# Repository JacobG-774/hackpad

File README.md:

# Tuxpad!
*A 6-key macropad with an OLED display, neopixel light bar, and circuitpython firmware, designed to simplify repetitive tasks.*

[PCB demo on KiCanvas](https://kicanvas.org/?repo=https%3A%2F%2Fgithub.com%2FJacobG-774%2Fhackpad%2Fblob%2Fmain%2FPCB%2Fhackpad.kicad_pcb)

**Features**

* Customizable macros to simplify productivity, gaming, or other workflows/applications
* RGB Neopixel bar for awesome customizable lighting
* OLED display for time, system information, or motivational messages

**Materials Used**

* Seeed XIAO RP2040 microcontroller - 1
* MX-style mechanical switches - 6
* 0.91” 128×32 OLED display - 1
* Blank DSA keycaps - 6
* SK6812 MINI-E RGB LEDs - 16
* M3×16mm screws - 4
In addition to the PCB and 3d printed case of course.

**How it Works**

I decided on direct wiring for the switches as matrix wiring would add complication and more possible failure points to the design while only saving one pin (which I wouldn't need anyways). The Neopixel LEDs can be individually controlled through the firmware and allow for full and relatively simple customizability. 
My choice of CircuitPython without KMK for the firmware might seem counterintuitive, but this enables me to more easily base lighting patterns or displays on the LCD off key presses (for example, the neopixels change color every key press, or the LCD displays my total key press count for the day to keep me motivated). I also couldn't find any documentation for direct wiring, OLED, or LED support in KMK, so it wasn't a very viable option.

**Credits/Acknowledgements**

I'm happy to say I mostly designed my case and PCB with just the help of the Hackpad tutorial, Google, and my few brain cells. The rendering was made with the help of [ohagel](https://www.thingiverse.com/thing:738769) and [gcb](https://www.thingiverse.com/thing:421524)'s files on Thingiverse, and I used a small amount of AI and reverse engineering from [LyricSantana](https://github.com/LyricSantana/lyrics_macropad/tree/main)'s code for the firmware.

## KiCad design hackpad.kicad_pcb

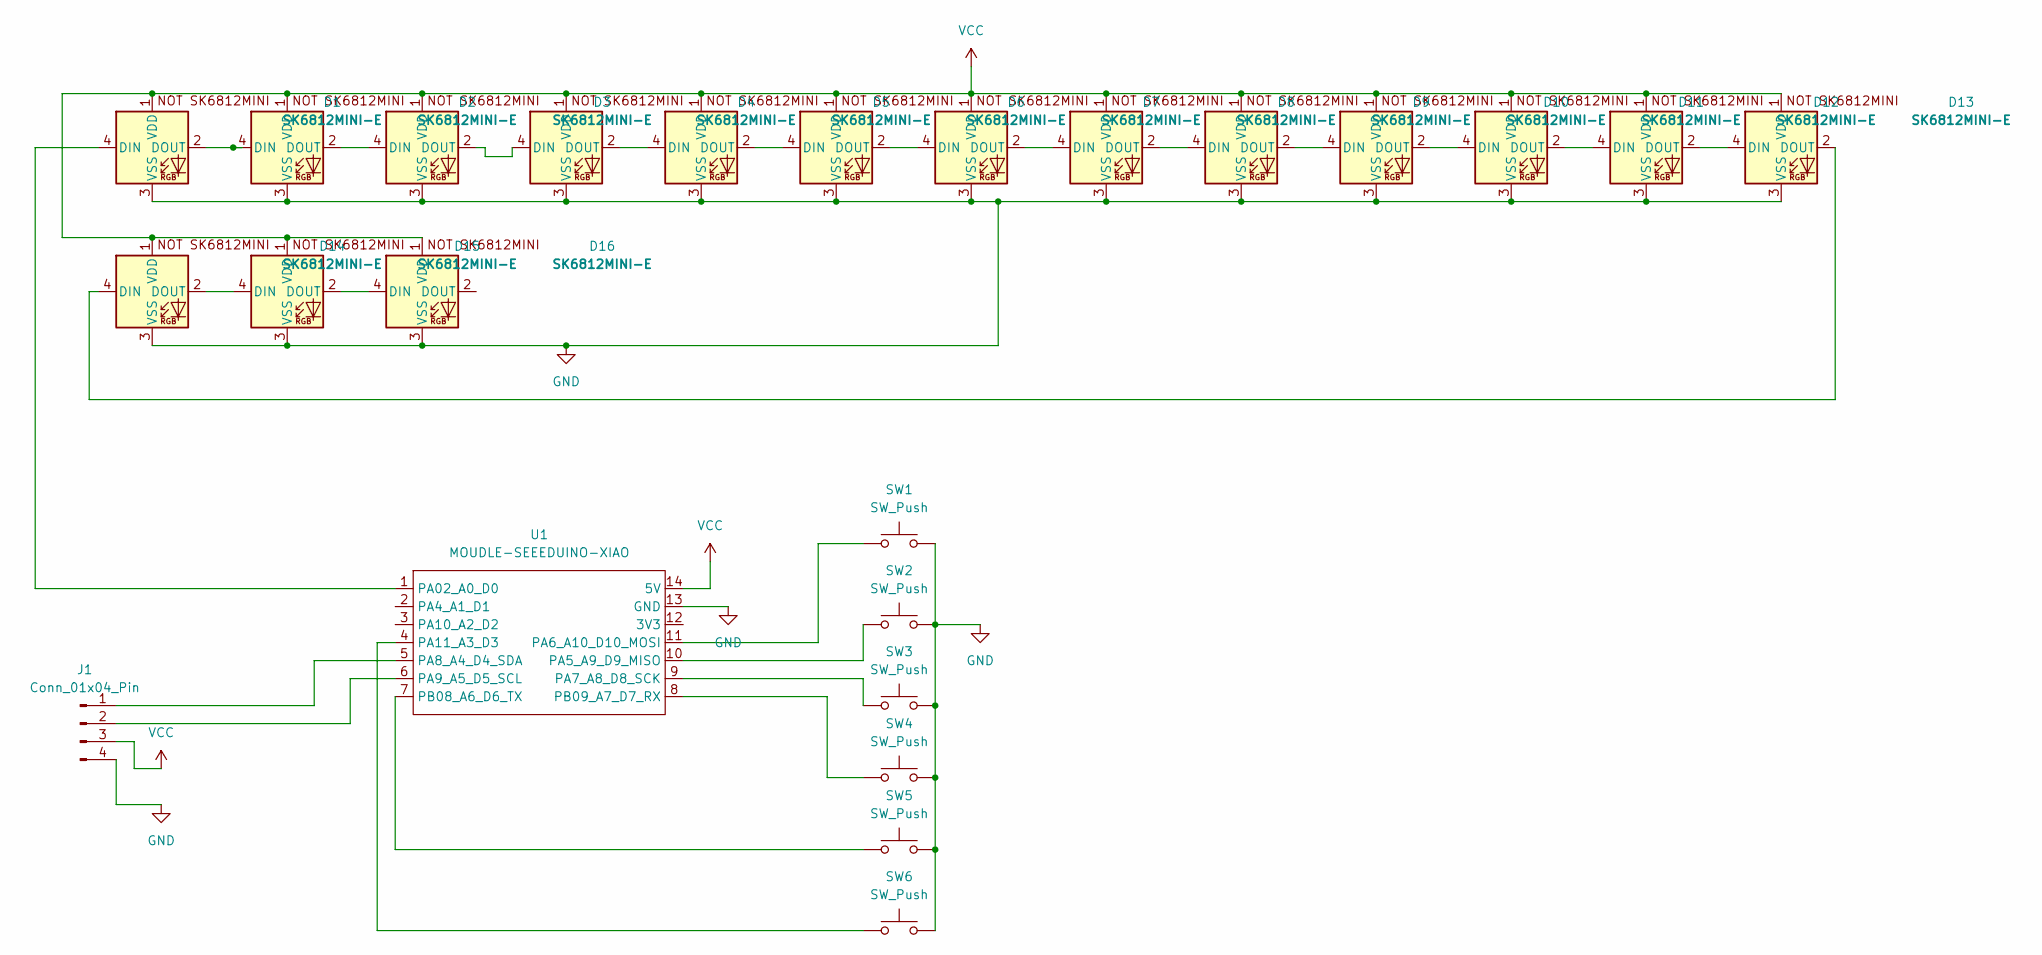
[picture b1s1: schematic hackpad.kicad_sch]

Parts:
D1, D2, D3, D4, D5, D6, D7, D8, D9, D10, D11, D12, D13, D14, D15, D16: SK6812MINI-E; SK6812MINI-E_fixed
J1: Conn_01x04_Pin; PinHeader_1x04_P2.54mm_Vertical
SW1, SW2, SW3, SW4, SW5, SW6: SW_Push; SW_Cherry_MX_1.00u_PCB
U1: MOUDLE-SEEEDUINO-XIAO; XIAO-Generic-Hybrid-14P-2.54-21X17.8MM

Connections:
GND: D1.3 (VSS), D2.3 (VSS), D3.3 (VSS), D4.3 (VSS), D5.3 (VSS), D6.3 (VSS), D7.3 (VSS), D8.3 (VSS), D9.3 (VSS), D10.3 (VSS), D11.3 (VSS), D12.3 (VSS), D13.3 (VSS), D14.3 (VSS), D15.3 (VSS), D16.3 (VSS), J1.4, SW1.2, SW2.2, SW3.2, SW4.2, SW5.2, SW6.2, U1.13 (GND)
unnamed: D1.4 (DIN), U1.1 (PA02_A0_D0)
unnamed: D1.2 (DOUT), D2.4 (DIN)
unnamed: D2.2 (DOUT), D3.4 (DIN)
unnamed: D3.2 (DOUT), D4.4 (DIN)
unnamed: D4.2 (DOUT), D5.4 (DIN)
unnamed: D5.2 (DOUT), D6.4 (DIN)
unnamed: D6.2 (DOUT), D7.4 (DIN)
unnamed: D7.2 (DOUT), D8.4 (DIN)
unnamed: D8.2 (DOUT), D9.4 (DIN)
unnamed: D9.2 (DOUT), D10.4 (DIN)
unnamed: D10.2 (DOUT), D11.4 (DIN)
unnamed: D11.2 (DOUT), D12.4 (DIN)
unnamed: D12.2 (DOUT), D13.4 (DIN)
unnamed: D13.2 (DOUT), D14.4 (DIN)
unnamed: D14.2 (DOUT), D15.4 (DIN)
unnamed: D15.2 (DOUT), D16.4 (DIN)
unnamed: J1.1, U1.5 (PA8_A4_D4_SDA)
unnamed: J1.2, U1.6 (PA9_A5_D5_SCL)
unnamed: SW2.1, U1.10 (PA5_A9_D9_MISO)
unnamed: SW1.1, U1.11 (PA6_A10_D10_MOSI)
unnamed: SW3.1, U1.9 (PA7_A8_D8_SCK)
unnamed: SW6.1, U1.4 (PA11_A3_D3)
unnamed: SW5.1, U1.7 (PB08_A6_D6_TX)
unnamed: SW4.1, U1.8 (PB09_A7_D7_RX)
VCC: D1.1 (VDD), D2.1 (VDD), D3.1 (VDD), D4.1 (VDD), D5.1 (VDD), D6.1 (VDD), D7.1 (VDD), D8.1 (VDD), D9.1 (VDD), D10.1 (VDD), D11.1 (VDD), D12.1 (VDD), D13.1 (VDD), D14.1 (VDD), D15.1 (VDD), D16.1 (VDD), J1.3, U1.14 (5V)

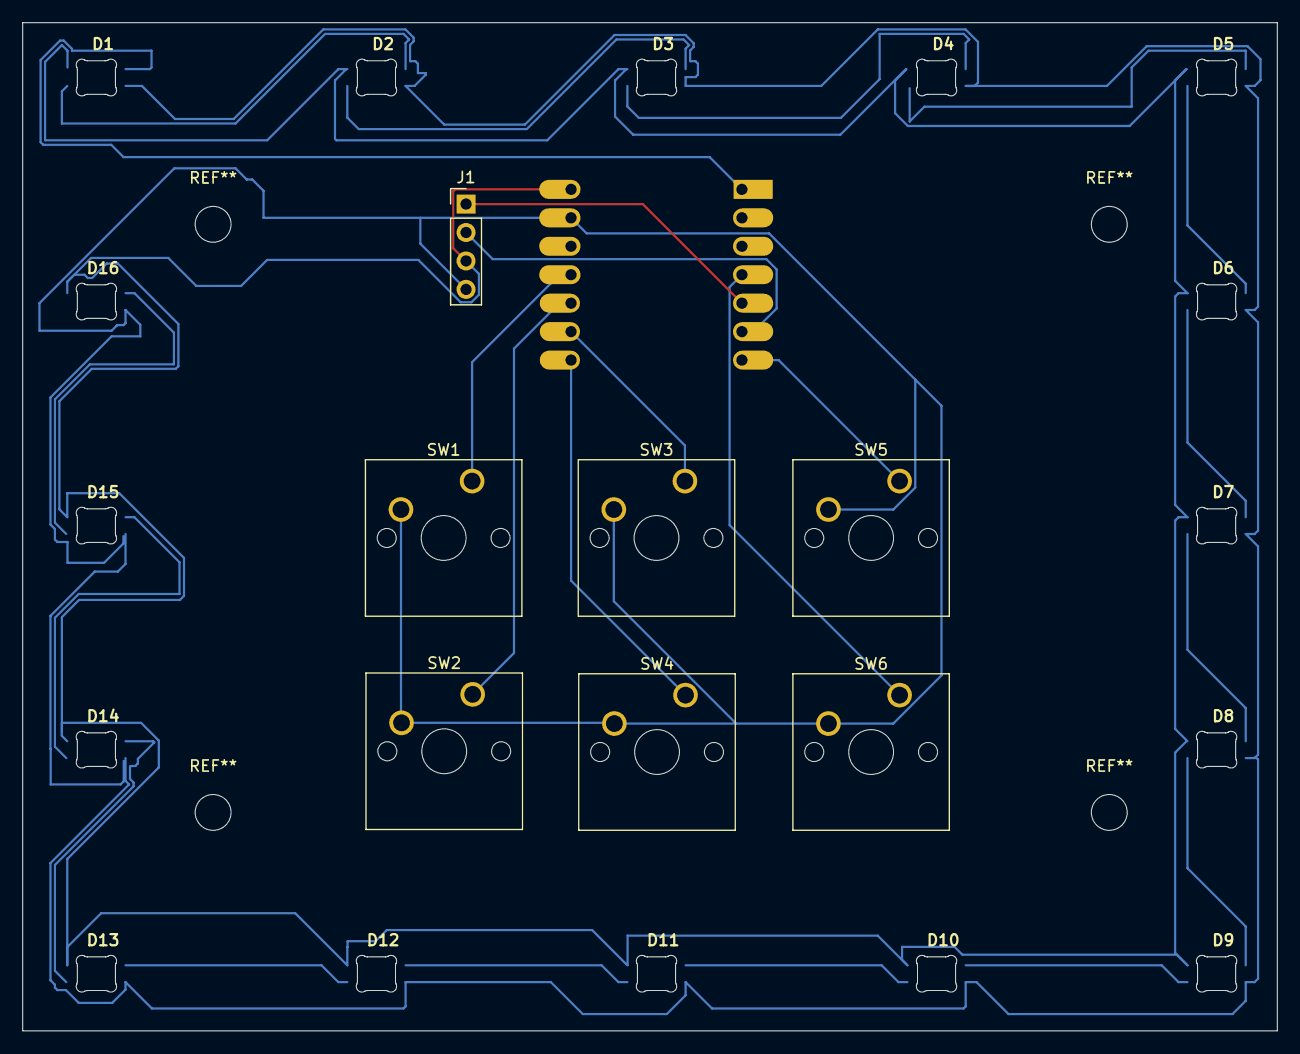
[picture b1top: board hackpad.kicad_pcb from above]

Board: 2 copper layers, 112.0 x 90.0 mm, 24 parts (1 on the bottom side), 26 nets.

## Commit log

2026-06-20 Added cad, pcb, and some production files.
2026-06-20 Rename Part Studio 1 - case_bottom.stl to production/Top.stl
2026-06-20 Rename Top.stl to Bottom.stl
2026-06-20 Rename Part Studio 1 - case_top.stl to production/Top.stl
2026-06-20 Rename Part Studio 1 - led_bar.stl to production/led_bar.stl
2026-06-20 Add assembled-model.STEP file
2026-06-20 Rename hackpad.kicad_pcb to PCB/hackpad.kicad_pcb
2026-06-20 Rename hackpad.kicad_sch to PCB/hackpad.kicad_sch
2026-06-20 Rename hackpad.kicad_pro to PCB/hackpad.kicad_pro
2026-06-22 Rename gerbers.zip to production/gerbers.zip
2026-06-22 Rename main.py to Firmware/main.py
2026-06-22 wrote readme
    Expanded project details, including components, schematic, and images.
2026-06-22 Updated the rendering image link in the README.
2026-06-22 worked more on readme
2026-06-23 Revise README for clarity and additional information
    Updated wording for clarity and added details about design choices and credits.
2026-06-23 Fix formatting in README credits section
